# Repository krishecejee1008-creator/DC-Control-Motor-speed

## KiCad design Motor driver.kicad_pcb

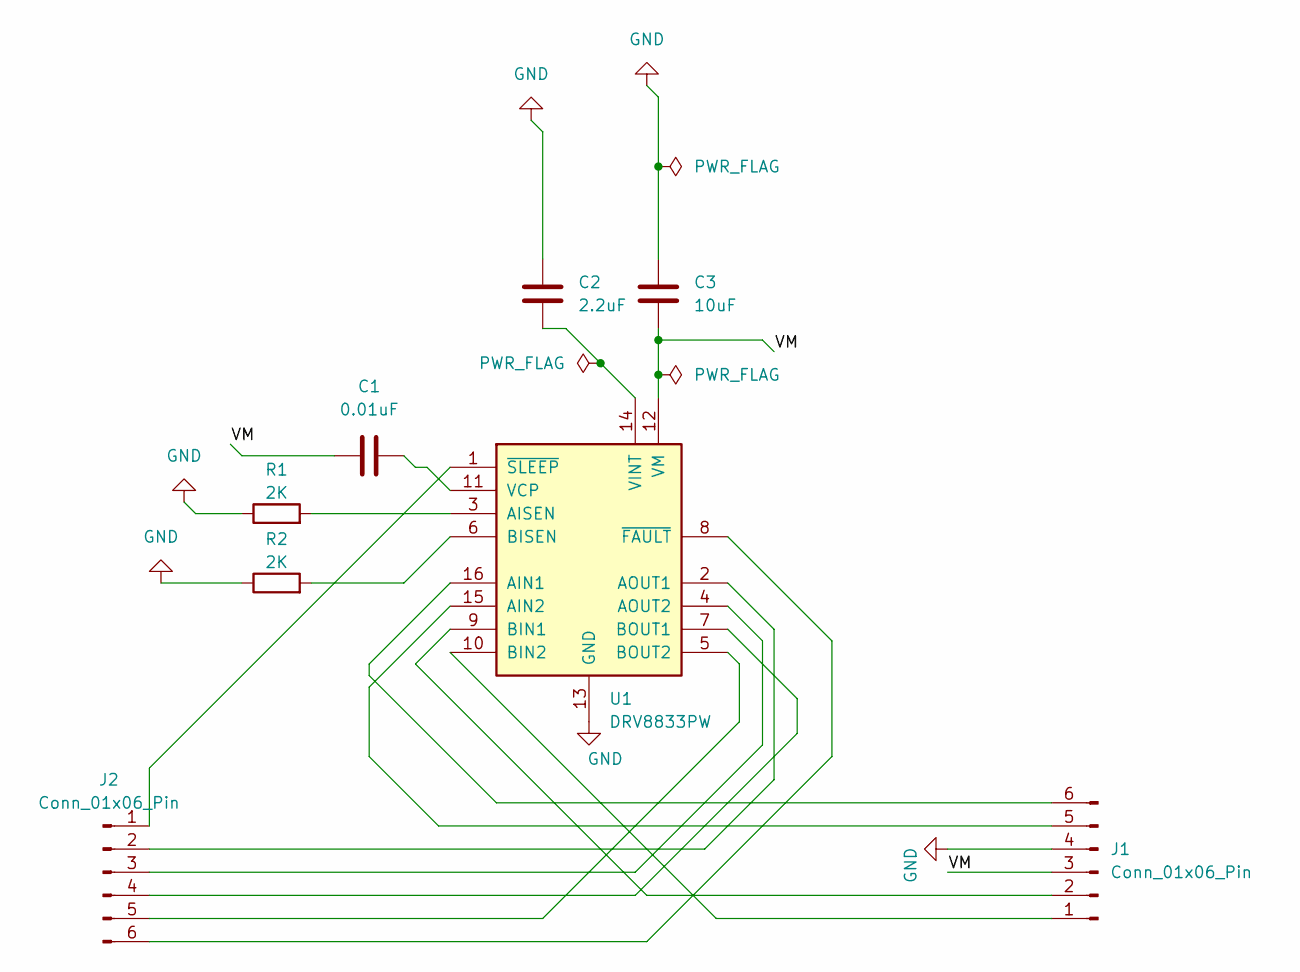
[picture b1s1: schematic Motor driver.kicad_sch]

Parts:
C1: 0.01uF; C_0805_2012Metric
C2: 2.2uF; C_0805_2012Metric
C3: 10uF; CP_EIA-6032-20_AVX-F
J1, J2: Conn_01x06_Pin; PinHeader_1x06_P2.54mm_Vertical
R1, R2: 2K; R_0805_2012Metric
U1: DRV8833PW; TSSOP-16_4.4x5mm_P0.65mm

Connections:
/VM: C1.2, C3.1, J1.3, U1.12 (VM)
GND: C2.2, C3.2, J1.4, R1.1, R2.1, U1.13 (GND)
unnamed: J1.1, U1.10 (BIN2)
unnamed: J1.2, U1.9 (BIN1)
unnamed: J1.5, U1.15 (AIN2)
unnamed: J1.6, U1.16 (AIN1)
unnamed: J2.1, U1.1 (~SLEEP)
unnamed: J2.2, U1.2 (AOUT1)
unnamed: J2.3, U1.4 (AOUT2)
unnamed: J2.4, U1.7 (BOUT1)
unnamed: J2.5, U1.5 (BOUT2)
unnamed: J2.6, U1.8 (~FAULT)
unnamed: R1.2, U1.3 (AISEN)
unnamed: R2.2, U1.6 (BISEN)
unnamed: C1.1, U1.11 (VCP)
unnamed: C2.1, U1.14 (VINT)

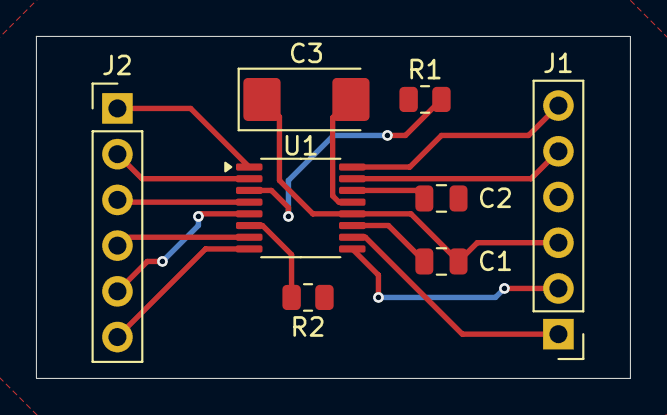
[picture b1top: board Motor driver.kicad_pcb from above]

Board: 2 copper layers, 33.0 x 19.0 mm, 8 parts (0 on the bottom side), 16 nets.
